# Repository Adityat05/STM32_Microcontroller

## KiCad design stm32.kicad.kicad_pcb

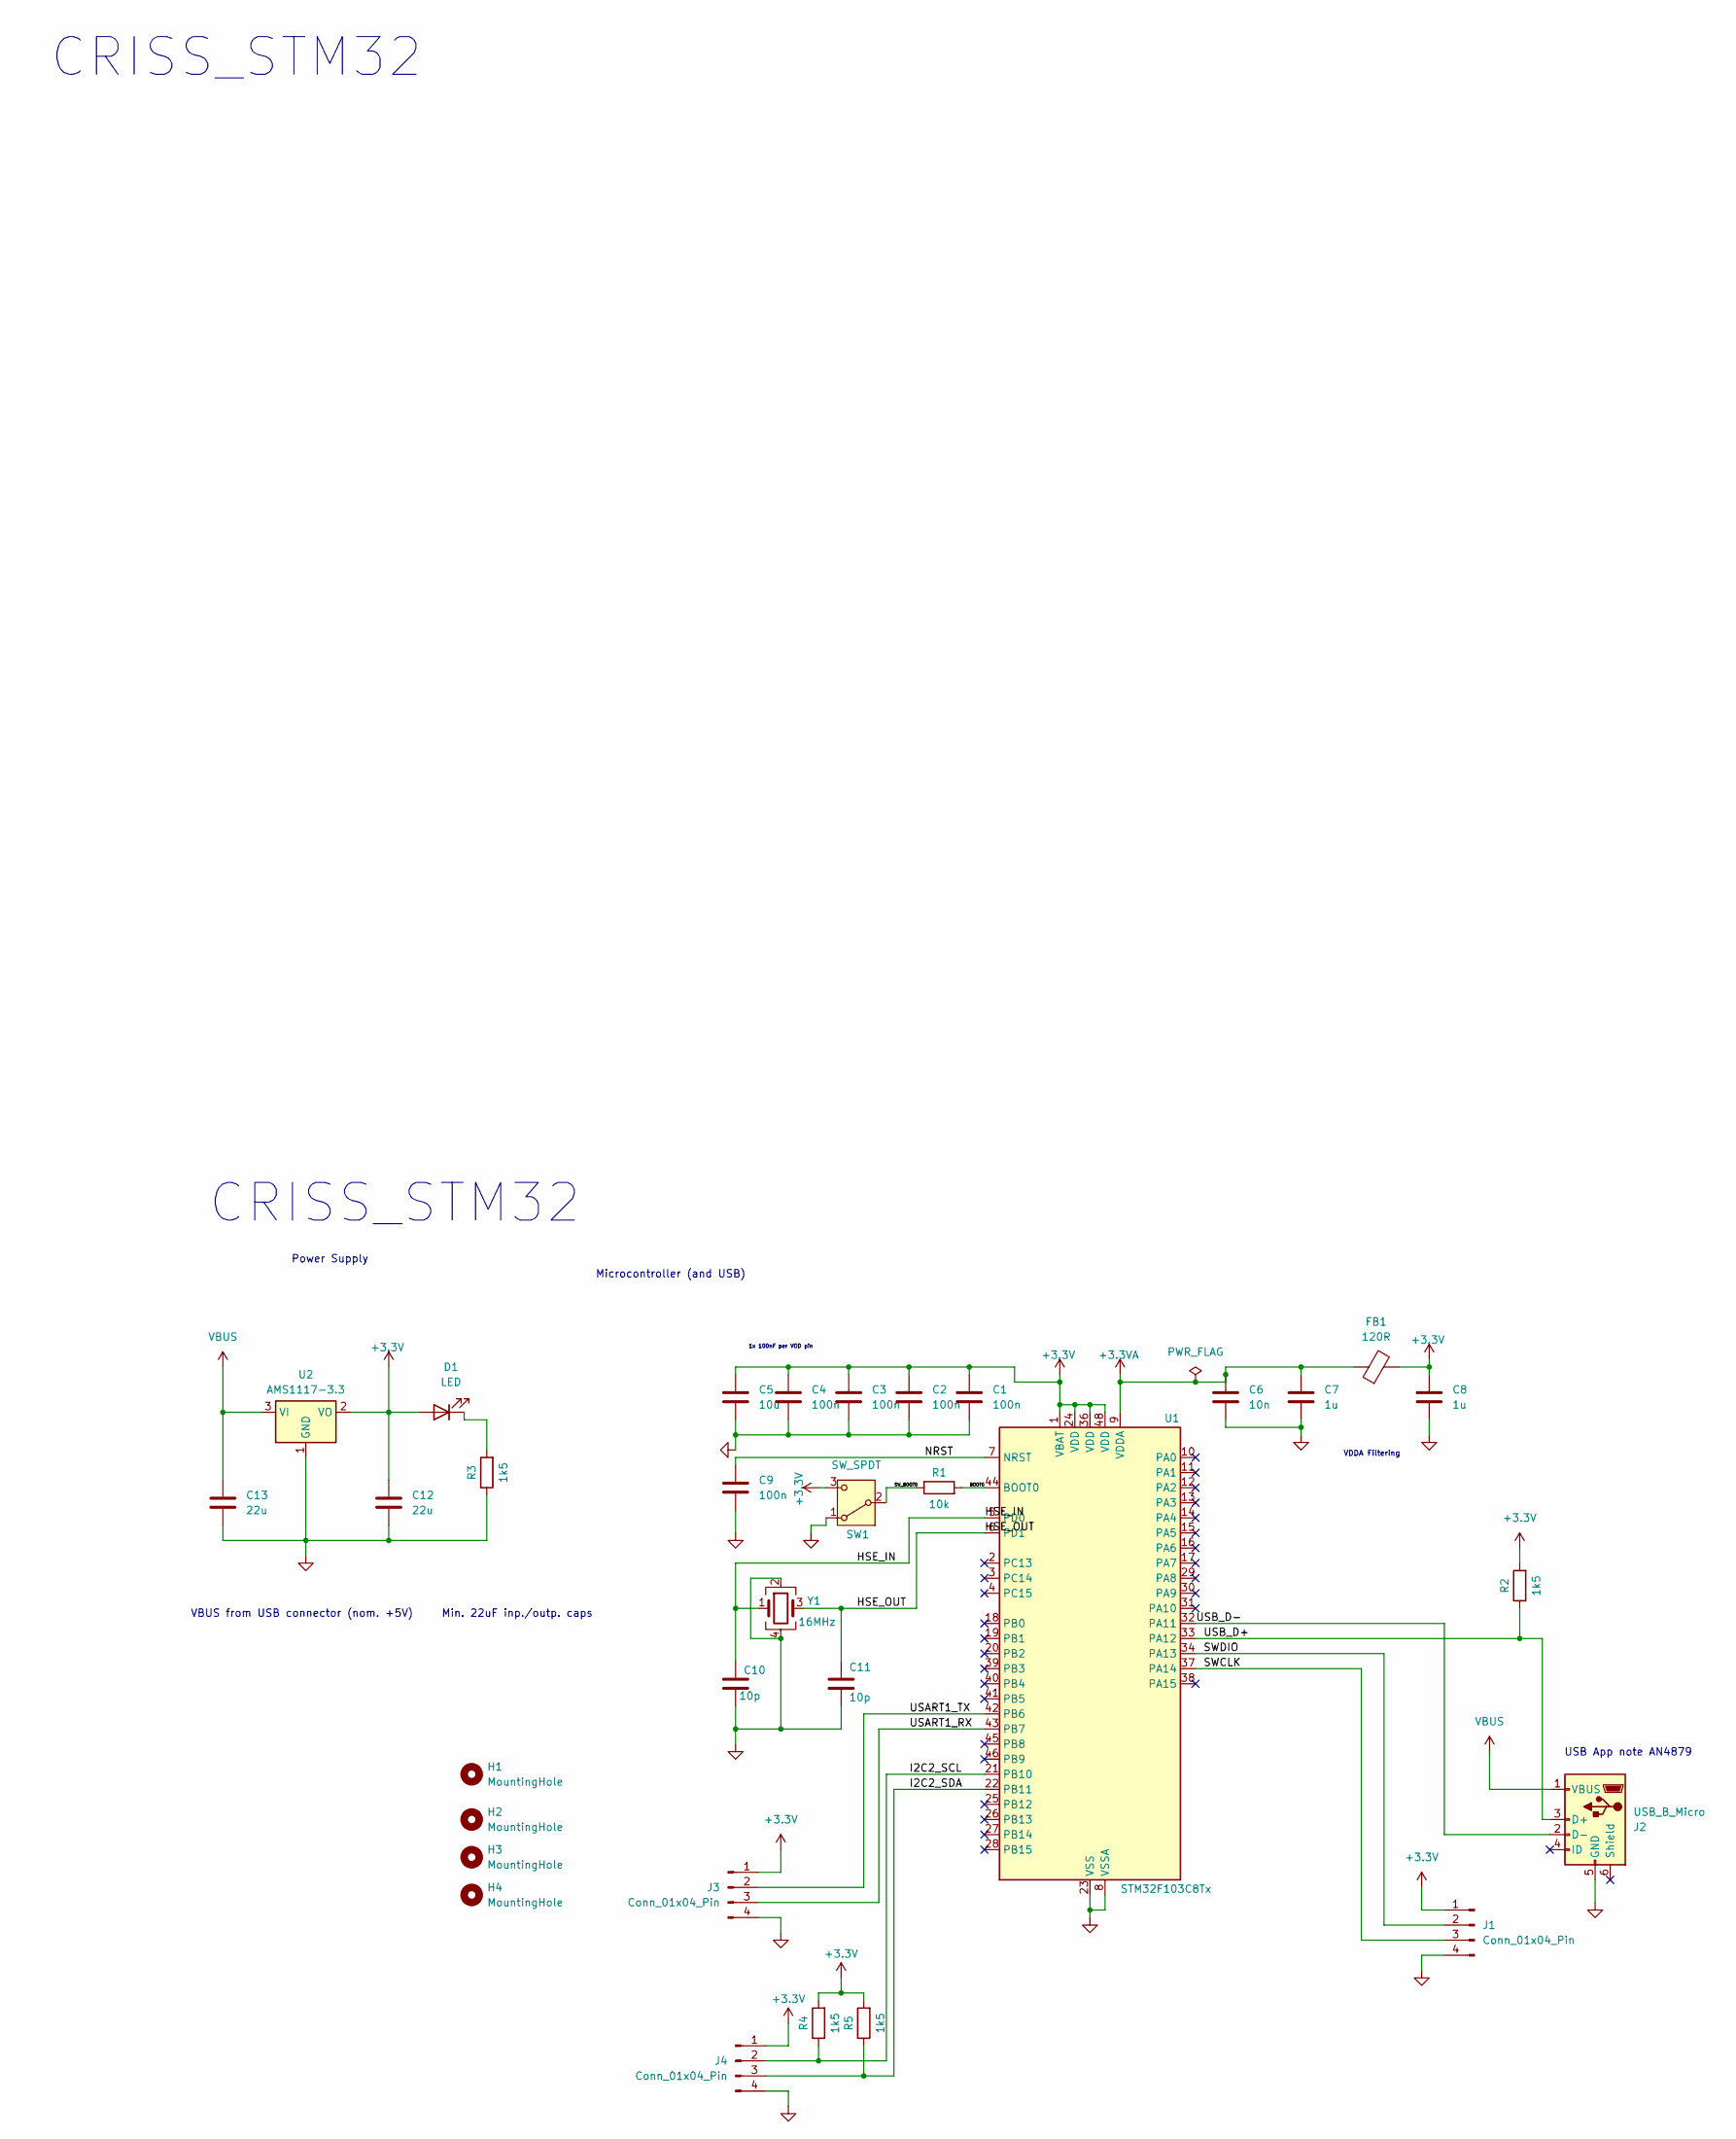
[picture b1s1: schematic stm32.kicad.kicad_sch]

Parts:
C1, C2, C3, C4, C9: 100n; C_0402_1005Metric
C5: 10u; C_0603_1608Metric
C6: 10n; C_0402_1005Metric
C7, C8: 1u; C_0402_1005Metric
C10, C11: 10p; C_0402_1005Metric
C12, C13: 22u; C_0805_2012Metric
D1: LED; LED_0603_1608Metric
FB1: 120R; L_0603_1608Metric
H1, H2, H3, H4: MountingHole; MountingHole_2.2mm_M2
J1, J3, J4: Conn_01x04_Pin; PinHeader_1x04_P2.54mm_Vertical
J2: USB_B_Micro; USB_Micro-B_Wuerth_629105150521
R1: 10k; R_0402_1005Metric
R2, R3, R4, R5: 1k5; R_0402_1005Metric
SW1: SW_SPDT; SW_SPDT_PCM12
U1: STM32F103C8Tx; LQFP-48_7x7mm_P0.5mm
U2: AMS1117-3.3; SOT-223-3_TabPin2
Y1: 16MHz; Crystal_SMD_3225-4Pin_3.2x2.5mm

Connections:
+3.3V: C1.1, C2.1, C3.1, C4.1, C5.1, C8.1, C12.1, D1.2 (A), FB1.2, J1.1, J3.1, J4.1, R2.2, R4.2, R5.2, SW1.3 (C), U1.1 (VBAT), U1.24 (VDD), U1.36 (VDD), U1.48 (VDD), U2.2 (VO)
+3.3VA: C6.1, C7.1, FB1.1, U1.9 (VDDA)
/BOOT0: R1.2, U1.44 (BOOT0)
/HSE_IN: C10.1, U1.5 (PD0), Y1.1
/HSE_OUT: C11.1, U1.6 (PD1), Y1.3
/I2C2_SCL: J4.2, R4.1, U1.21 (PB10)
/I2C2_SDA: J4.3, R5.1, U1.22 (PB11)
/NRST: C9.1, U1.7 (NRST)
/SWCLK: J1.3, U1.37 (PA14)
/SWDIO: J1.2, U1.34 (PA13)
/SW_BOOT0: R1.1, SW1.2 (B)
/USART1_RX: J3.3, U1.43 (PB7)
/USART1_TX: J3.2, U1.42 (PB6)
/USB_D+: J2.3 (D+), R2.1, U1.33 (PA12)
/USB_D-: J2.2 (D-), U1.32 (PA11)
GND: C1.2, C2.2, C3.2, C4.2, C5.2, C6.2, C7.2, C8.2, C9.2, C10.2, C11.2, C12.2, C13.2, J1.4, J2.5 (GND), J3.4, J4.4, R3.1, SW1.1 (A), U1.8 (VSSA), U1.23 (VSS), U1.35 (VSS), U1.47 (VSS), U2.1 (GND), Y1.2, Y1.4
unnamed: D1.1 (K), R3.2
VBUS: C13.1, J2.1 (VBUS), U2.3 (VI)

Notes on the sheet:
CRISS_STM32
CRISS_STM32
Microcontroller (and USB)
VDDA Filtering
Power Supply
USB App note AN4879
1x 100nF per VOD pin
VBUS from USB connector (nom. +5V) Min. 22uF inp./outp. caps

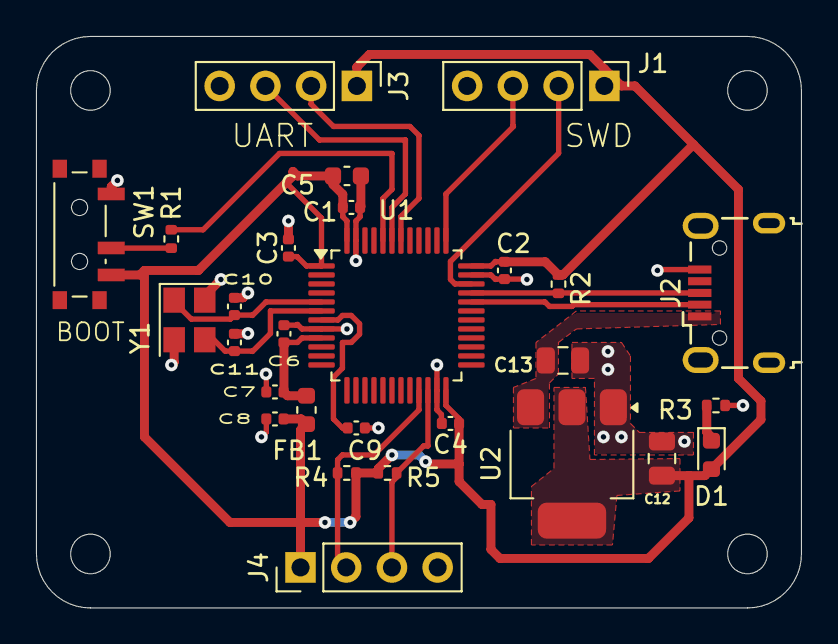
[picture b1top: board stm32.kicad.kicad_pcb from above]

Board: 2 copper layers, 42.5 x 31.8 mm, 32 parts (0 on the bottom side), 18 nets.

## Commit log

2025-03-15 second commit
